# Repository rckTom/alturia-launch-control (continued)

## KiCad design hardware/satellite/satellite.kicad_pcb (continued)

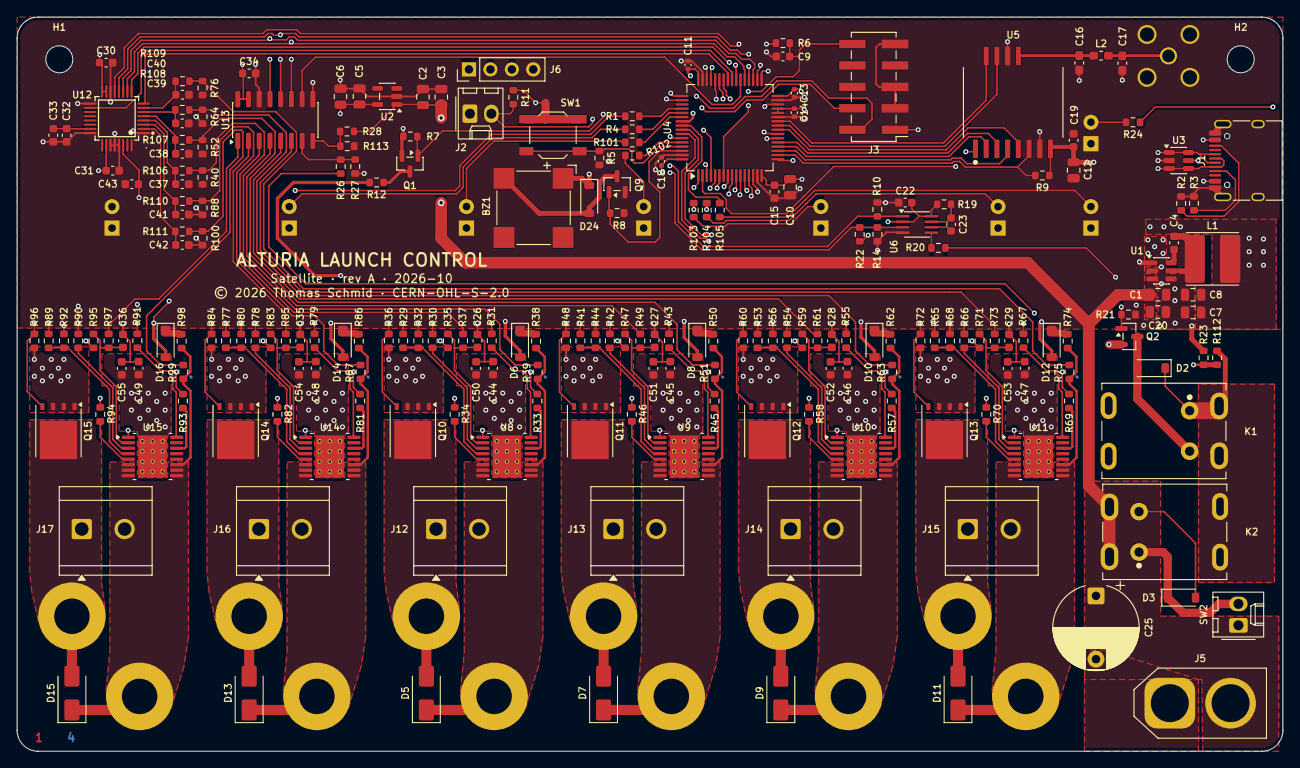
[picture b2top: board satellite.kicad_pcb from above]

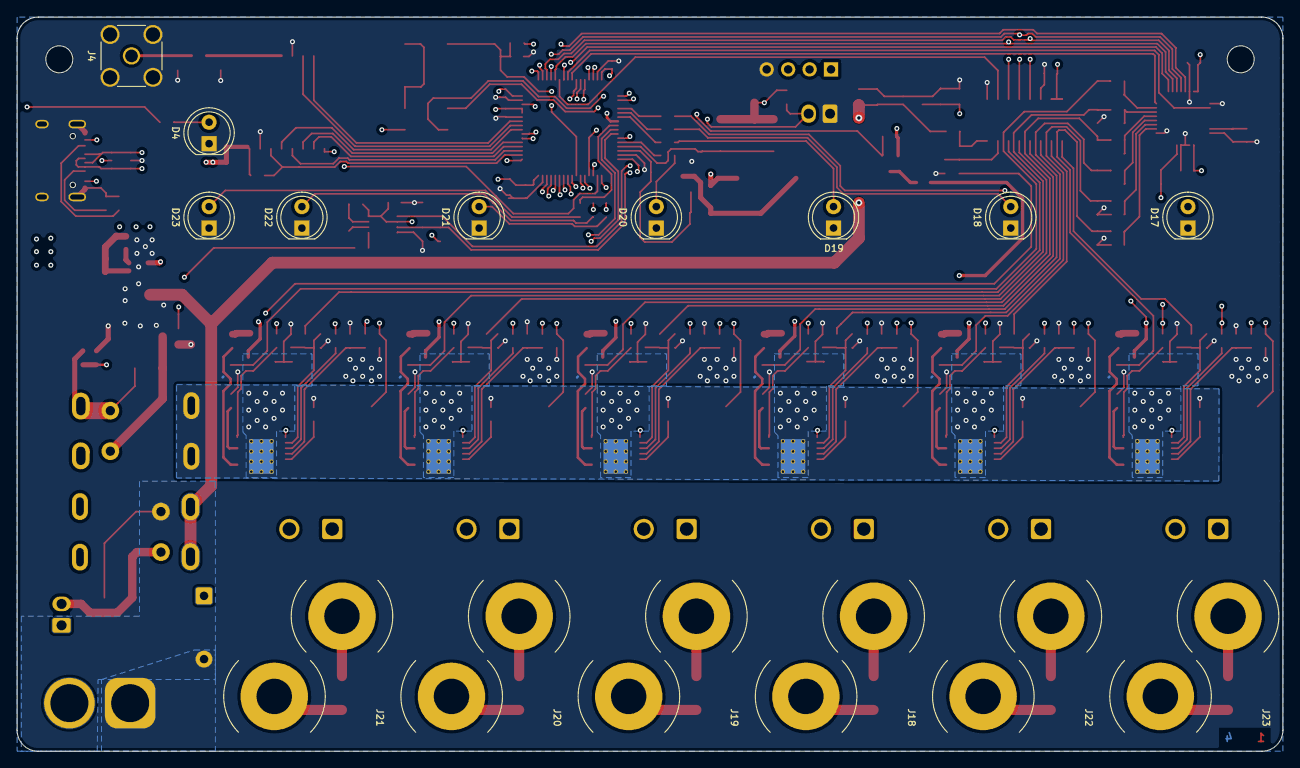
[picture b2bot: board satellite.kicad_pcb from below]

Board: 4 copper layers, 150.0 x 87.0 mm, 233 parts (15 on the bottom side), 156 nets.

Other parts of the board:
C12: 10u; C_0805_2012Metric
C19, C43, C44, C45, C46, C47, C48, C49, C50, C51, C52, C53, C54, C55: 100n; C_0603_1608Metric
R11: 10k 1%; R_0603_1608Metric

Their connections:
+3V3: C12.1, C19.1, R11.1; also elsewhere on the board
CONT_TEST_REQ: R11.2; also elsewhere on the board
GND: C12.2, C19.2, C43.2, C44.1, C45.1, C46.1, C47.1, C48.1, C49.1, C50.1, C51.1, C52.1, C53.1, C54.1, C55.1; also elsewhere on the board
V_PYRO_ARMED: C44.2, C45.2, C46.2, C47.2, C48.2, C49.2, C50.2, C51.2, C52.2, C53.2, C54.2, C55.2; also elsewhere on the board
V_TEST: C43.1; also elsewhere on the board

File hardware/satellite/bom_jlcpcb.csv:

"Comment","Designator","Footprint","LCSC Part #"
"Buzzer","BZ1","MagneticBuzzer_CUI_CMT-8504-100-SMT","C94599"
"10u","C1,C2,C5,C12,C20","C_0805_2012Metric","C440198"
"1u","C3","C_0805_2012Metric","C28323"
"100n","C4,C9,C19,C22,C26,C27,C28,C29,C30,C33,C35,C36,C37,C38,C39,C40,C41,C42,C43,C44,C45,C46,C47,C48,C49,C50,C51,C52,C53,C54,C55","C_0603_1608Metric","C14663"
"2.2u","C6","C_0805_2012Metric","C19110"
"22u","C7,C8","C_0805_2012Metric","C45783"
"4.7uF","C10","C_0805_2012Metric","C98195"
"100nF","C11,C13,C14,C18","C_0402_1005Metric","C307331"
"1u","C15,C23,C32,C34","C_0603_1608Metric","C5199872"
"330n","C31","C_0603_1608Metric","C107070"
"1N4148W","D2,D3,D6,D8,D10,D12,D14,D16,D24","D_SOD-123","C81598"
"SS34","D5,D7,D9,D11,D13,D15","D_SMA","C8678"
"TYPE-C 16P","J1","USB_C_Receptacle_HRO_TYPE-C-31-M-12","C2765186"
"ACTL3CR3V","K1,K2","RELAY-TH_ACTL3CR3","C6118826"
"10uH","L1","L_Cenker_CKCS6045","C168076"
"AO3401A","Q1","SOT-23","C15127"
"AO3400A","Q2,Q9","SOT-23","C20917"
"CSD17307Q5A","Q10,Q11,Q12,Q13,Q14,Q15","TDSON-8-1","C139362"
"560 1%","R1,R4,R35,R47,R59,R71,R83,R95,R101,R102,R103,R104,R105","R_0603_1608Metric","C23204"
"5.1k 1%","R2,R3","R_0603_1608Metric","C23186"
"10k 1%","R5,R6,R7,R8,R9,R10,R11,R14,R21,R32,R33,R36,R44,R45,R48,R56,R57,R60,R68,R69,R72,R80,R81,R84,R92,R93,R96,R106,R107,R108,R109,R110,R111","R_0603_1608Metric","C25804"
"270","R12","R_0603_1608Metric","C22966"
"150k 1%","R19","R_0603_1608Metric","C22807"
"1k 1%","R20,R23,R27,R38,R40,R50,R52,R62,R64,R74,R76,R86,R88,R98,R100,R113","R_0603_1608Metric","C21190"
"3k3 1%","R24,R26,R28,R39,R51,R63,R75,R87,R99,R112","R_0603_1608Metric","C22978"
"100 1%","R29,R30,R31,R37,R41,R42,R43,R49,R53,R54,R55,R61,R65,R66,R67,R73,R77,R78,R79,R85,R89,R90,R91,R97","R_0603_1608Metric","C22775"
"6k8 1%","R34,R46,R58,R70,R82,R94","R_0603_1608Metric","C23212"
"BOOT0","SW1","SW_SPST_TL3342","C318884"
"AP63203WU","U1","TSOT-23-6","C780769"
"TPS70933DBVR","U2","SOT-23-5","C89347"
"USBLC6-2SC6","U3","SOT-23-6","C2687116"
"STM32G474RET6","U4","LQFP-64_10x10mm_P0.5mm","C521608"
"SN74LVC1G123","U6","SSOP-8_2.95x2.8mm_P0.65mm","C123302"
"TPS1HB08AQPWPRQ1","U8,U9,U10,U11,U14,U15","HTSSOP-16-1EP_4.4x5mm_P0.65mm_EP3.4x5mm_Mask2.78x3.37mm_ThermalVias03","C3019223"
"ADS124S08IPBSR","U12","TQFP-32_L5.0-W5.0-P0.50-LS7.0-TL","C2870171"
"MCP3208","U13","SOIC-16_3.9x9.9mm_P1.27mm","C626764"

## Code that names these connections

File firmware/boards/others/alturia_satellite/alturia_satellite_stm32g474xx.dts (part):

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 * schematic (CH(6 - n) is channel n).
 *
 * There is no HSE crystal: the core runs from HSI16 through the PLL, USB
 * from HSI48 trimmed by CRS (board.c). PF0/PF1 are channel 6's enables and
 * PC14 is ARM_ENABLE, so neither clk_hse nor clk_lse may be enabled.
 */

/dts-v1/;
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		compatible = "gpio-leds";

		status_led: status_led {
			gpios = <&gpiob 3 GPIO_ACTIVE_HIGH>;	/* LED_STATUS, D23 */
		};
	};

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	chan_leds {
		compatible = "gpio-leds";

		chan_led1: chan_led1 { gpios = <&gpioa 8 GPIO_ACTIVE_HIGH>; };	/* LED_CHN_6 */
		chan_led2: chan_led2 { gpios = <&gpioa 9 GPIO_ACTIVE_HIGH>; };	/* LED_CHN_5 */
		chan_led3: chan_led3 { gpios = <&gpiob 7 GPIO_ACTIVE_HIGH>; };	/* LED_CHN_4 */
		chan_led4: chan_led4 { gpios = <&gpioc 12 GPIO_ACTIVE_HIGH>; };	/* LED_CHN_3 */
		chan_led5: chan_led5 { gpios = <&gpioc 11 GPIO_ACTIVE_HIGH>; };	/* LED_CHN_2 */
		chan_led6: chan_led6 { gpios = <&gpioc 10 GPIO_ACTIVE_HIGH>; };	/* LED_CHN_1 */
	};

	/* Pyro channel control lines: TPS1HB08 enables (through 100 R) and the
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	pyro_enables {
		compatible = "gpio-leds";

		en_h1: en_h1 { gpios = <&gpioa 3 GPIO_ACTIVE_HIGH>; };	/* ENABLE_P6_HIGH */
		en_h2: en_h2 { gpios = <&gpioc 5 GPIO_ACTIVE_HIGH>; };	/* ENABLE_P5_HIGH */
		en_h3: en_h3 { gpios = <&gpioa 1 GPIO_ACTIVE_HIGH>; };	/* ENABLE_P4_HIGH */
		en_h4: en_h4 { gpios = <&gpioc 3 GPIO_ACTIVE_HIGH>; };	/* ENABLE_P3_HIGH */
		en_h5: en_h5 { gpios = <&gpioc 1 GPIO_ACTIVE_HIGH>; };	/* ENABLE_P2_HIGH */
		en_h6: en_h6 { gpios = <&gpiof 1 GPIO_ACTIVE_HIGH>; };	/* ENABLE_P1_HIGH */
		en_l1: en_l1 { gpios = <&gpioc 4 GPIO_ACTIVE_HIGH>; };	/* ENABLE_P6_LOW */
		en_l2: en_l2 { gpios = <&gpioa 2 GPIO_ACTIVE_HIGH>; };	/* ENABLE_P5_LOW */
		en_l3: en_l3 { gpios = <&gpioa 0 GPIO_ACTIVE_HIGH>; };	/* ENABLE_P4_LOW */
		en_l4: en_l4 { gpios = <&gpioc 2 GPIO_ACTIVE_HIGH>; };	/* ENABLE_P3_LOW */
		en_l5: en_l5 { gpios = <&gpioc 0 GPIO_ACTIVE_HIGH>; };	/* ENABLE_P2_LOW */
		en_l6: en_l6 { gpios = <&gpiof 0 GPIO_ACTIVE_HIGH>; };	/* ENABLE_P1_LOW */
		hs_latch: hs_latch {
			gpios = <&gpiob 4 GPIO_ACTIVE_HIGH>;	/* COMMON_HIGH_SIDE_LATCH */
		};
		hs_dia_en: hs_dia_en {
			gpios = <&gpiob 5 GPIO_ACTIVE_HIGH>;	/* COMMON_HIGH_SIDE_DIA_EN */
		};
	};

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		compatible = "gpio-leds";

		arm_pump: arm_pump {
			gpios = <&gpiob 6 GPIO_ACTIVE_HIGH>;	/* ARM_PUMP -> U6 A */
		};
		arm_enable: arm_enable {
			gpios = <&gpioc 14 GPIO_ACTIVE_HIGH>;	/* ARM_ENABLE -> U6 CLR */
		};
		cont_en: cont_en {
			gpios = <&gpioa 10 GPIO_ACTIVE_LOW>;	/* CONT_EN, Q1 gate */
		};
	};

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		compatible = "gpio-keys";

		pair_button: pair_button {
			gpios = <&gpioc 15 GPIO_ACTIVE_LOW>;	/* CONT_TEST_REQ */
			zephyr,code = <INPUT_KEY_0>;
		};
	};

	/* VKEY through the 3k3/1k divider: the key relay K2 has closed. PD2
	 * shares EXTI line 2 with LORA_DIO1 on PB2, so it is polled.
	 */
	key_switch {
		compatible = "gpio-keys";
		polling-mode;

		key_enabled: key_enabled {
			gpios = <&gpiod 2 GPIO_ACTIVE_HIGH>;	/* KEY_ENABLED */
			zephyr,code = <INPUT_KEY_1>;
		};
	};
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
/* Schematic net names, so the GPIO shell can address pins by them. */
&gpioa {
	gpio-line-names = "ENABLE_P4_LOW", "ENABLE_P4_HIGH", "ENABLE_P5_LOW", "ENABLE_P6_HIGH",
			  "LORA_NSS", "LORA_SCK", "LORA_MISO", "LORA_MOSI",
			  "LED_CHN_6", "LED_CHN_5", "CONT_EN", "USB_DN",
			  "USB_DP", "SWDIO", "SWCLK", "";
};

&gpiob {
	gpio-line-names = "LORA_RST", "LORA_BUSY", "LORA_DIO1", "LED_STATUS",
			  "COMMON_HIGH_SIDE_LATCH", "COMMON_HIGH_SIDE_DIA_EN", "ARM_PUMP", "LED_CHN_4",
			  "BOOT0", "BUZZER", "U0RXD", "U0TXD",
			  "SPI_ADC_24BIT_CS", "SPI_ADC_CLK", "SPI_ADC_MISO", "SPI_ADC_MOSI";
};

&gpioc {
	gpio-line-names = "ENABLE_P2_LOW", "ENABLE_P2_HIGH", "ENABLE_P3_LOW", "ENABLE_P3_HIGH",
			  "ENABLE_P6_LOW", "ENABLE_P5_HIGH", "SPI_ADC_12BIT_CS", "24BIT_ADC_DRDY",
			  "24BIT_ADC_RESET", "24BIT_ADC_START", "LED_CHN_1", "LED_CHN_2",
			  "LED_CHN_3", "LORA_RF_SW", "ARM_ENABLE", "CONT_TEST_REQ";
};

&gpiod {
	gpio-line-names = "", "", "KEY_ENABLED";
};

&gpiof {
	gpio-line-names = "ENABLE_P1_LOW", "ENABLE_P1_HIGH";
};

&clk_lsi {
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&spi1 {
	pinctrl-0 = <&spi1_sck_pa5 &spi1_miso_pa6 &spi1_mosi_pa7>;
	pinctrl-names = "default";
	cs-gpios = <&gpioa 4 GPIO_ACTIVE_LOW>;	/* LORA_NSS, 10k pull-up */
	status = "okay";

	lora: sx1262@0 {
		compatible = "semtech,sx1262";
		reg = <0>;
		spi-max-frequency = <DT_FREQ_M(8)>;
		reset-gpios = <&gpiob 0 GPIO_ACTIVE_LOW>;	/* LORA_RST */
		busy-gpios = <&gpiob 1 GPIO_ACTIVE_HIGH>;	/* LORA_BUSY */
		dio1-gpios = <&gpiob 2 GPIO_ACTIVE_HIGH>;	/* LORA_DIO1 */
		antenna-enable-gpios = <&gpioc 13 GPIO_ACTIVE_HIGH>;	/* LORA_RF_SW */
		dio2-tx-enable;
		dio3-tcxo-voltage = <SX126X_DIO3_TCXO_1V8>;
		tcxo-power-startup-delay-ms = <5>;
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&spi2 {
	pinctrl-0 = <&spi2_sck_pb13 &spi2_miso_pb14 &spi2_mosi_pb15>;
	pinctrl-names = "default";
	cs-gpios = <&gpiob 12 GPIO_ACTIVE_LOW>,	/* SPI_ADC_24BIT_CS */
		   <&gpioc 6 GPIO_ACTIVE_LOW>;	/* SPI_ADC_12BIT_CS */
	status = "okay";

	adc_continuity: ads124s08@0 {
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
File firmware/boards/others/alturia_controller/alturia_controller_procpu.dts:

/*
 * Alturia Launch Control controller, rev A
 * (hardware/controller/pcb, ESP32-S3-WROOM-1-N16R2).
 *
 * Console and shell are on USB-C, which goes straight to the ESP32-S3's
 * USB Serial/JTAG. UART0's pins drive the LCD, so there is no UART.
 *
 * The controls are pushbuttons to GND with no external pull-ups. The front
 * panel has no arm key switch.
 */
/dts-v1/;

#include <espressif/esp32s3/esp32s3.dtsi>
#include <zephyr/dt-bindings/input/input-event-codes.h>
#include <zephyr/dt-bindings/lora/sx126x.h>
#include <zephyr/dt-bindings/pwm/pwm.h>
#include <espressif/partitions_0x0_amp_16M.dtsi>
#include "alturia_controller-pinctrl.dtsi"

/ {
	model = "Alturia Launch Control controller";
	compatible = "alturia,controller";

	aliases {
		led0 = &status_led;
		lora0 = &lora;
		buzzer = &buzzer;
		watchdog0 = &wdt0;
		fuel-gauge0 = &fuel_gauge;
		charger0 = &charger;
	};

	chosen {
		zephyr,sram = &sram1;
		zephyr,console = &usb_serial;
		zephyr,shell-uart = &usb_serial;
		zephyr,flash = &flash0;
		zephyr,code-partition = &slot0_partition;
		zephyr,display = &sharp_lcd;
	};

	leds {
		compatible = "gpio-leds";

		status_led: status_led {
			gpios = <&gpio1 10 GPIO_ACTIVE_HIGH>;	/* IO42, STATUS_LED */
		};
	};

	/* Passive magnetic buzzer QMB-09B-03; it needs a tone, not a level. */
	buzzer: buzzer {
		compatible = "pwm-buzzer";
		pwms = <&ledc0 0 PWM_HZ(4000) PWM_POLARITY_NORMAL>;	/* IO46 */
	};

	/* Key codes are the ones the controller app listens for. */
	ctrl_keys: ctrl_keys {
		compatible = "gpio-keys";
		debounce-interval-ms = <20>;

		/* Delock 22032 pushbuttons on J3 / J2 */
		arm_button {
			gpios = <&gpio0 8 (GPIO_PULL_UP | GPIO_ACTIVE_LOW)>;	/* KEY_ARM */
			zephyr,code = <INPUT_KEY_A>;
		};

		fire_button {
			gpios = <&gpio0 5 (GPIO_PULL_UP | GPIO_ACTIVE_LOW)>;	/* KEY_FIRE */
			zephyr,code = <INPUT_KEY_SPACE>;
		};

		fill_button {
			gpios = <&gpio0 3 (GPIO_PULL_UP | GPIO_ACTIVE_LOW)>;	/* KEY_FILL */
			zephyr,code = <INPUT_KEY_F>;
		};

		vent_button {
			gpios = <&gpio0 6 (GPIO_PULL_UP | GPIO_ACTIVE_LOW)>;	/* KEY_VENT */
			zephyr,code = <INPUT_KEY_V>;
		};

		/* D-pad SW1..SW6 */
		key_up {
			gpios = <&gpio0 1 (GPIO_PULL_UP | GPIO_ACTIVE_LOW)>;	/* KEY_UP */
			zephyr,code = <INPUT_KEY_UP>;
		};

		key_down {
			gpios = <&gpio0 4 (GPIO_PULL_UP | GPIO_ACTIVE_LOW)>;	/* KEY_DOWN */
			zephyr,code = <INPUT_KEY_DOWN>;
		};

		key_left {
			gpios = <&gpio0 2 (GPIO_PULL_UP | GPIO_ACTIVE_LOW)>;	/* KEY_LEFT */
			zephyr,code = <INPUT_KEY_LEFT>;
		};

		key_right {
			gpios = <&gpio0 7 (GPIO_PULL_UP | GPIO_ACTIVE_LOW)>;	/* KEY_RIGHT */
			zephyr,code = <INPUT_KEY_RIGHT>;
		};

		key_enter {
			gpios = <&gpio0 0 (GPIO_PULL_UP | GPIO_ACTIVE_LOW)>;	/* KEY_ENTER, BOOT strap */
			zephyr,code = <INPUT_KEY_ENTER>;
		};

		key_back {
			gpios = <&gpio0 9 (GPIO_PULL_UP | GPIO_ACTIVE_LOW)>;	/* KEY_BACK */
			zephyr,code = <INPUT_KEY_BACK>;
		};

		/* SW101 through Q105, 100k pull-up on board. Held for 6-9 s, the
		 * latch switches off by itself. A press held since power-on is
		 * not reported: gpio-keys only reports changes.
		 */
		power_button {
			gpios = <&gpio0 18 GPIO_ACTIVE_LOW>;	/* PWR_BTN */
			zephyr,code = <INPUT_KEY_POWER>;
		};
	};

	zephyr,user {
		/* Soft power latch (power_latch sheet): PWR_OFF high drops the
		 * 3V3_EN latch, unless the power button holds it.
		 */
		pwr-off-gpios = <&gpio0 21 GPIO_ACTIVE_HIGH>;
		/* BQ24296M PG: low while USB power is good */
		usb-pgood-gpios = <&gpio1 9 GPIO_ACTIVE_LOW>;	/* IO41 */
	};
};

/* 160 MHz instead of 240: the UI and the link need far less, and the CPU
 * mostly sleeps, so it is the awake current that counts.
 */
&cpu0 {
	clock-frequency = <ESP32_CLK_CPU_PLL_160M>;
};

/* Wakes light sleep (CONFIG_PM) for the kernel's next timeout */
&rtc_timer {
	status = "okay";
	wakeup-source;
};

&flash0 {
	reg = <0x0 DT_SIZE_M(16)>;
	ranges = <0x0 0x0 DT_SIZE_M(16)>;
};

&usb_serial {
	status = "okay";
};

&gpio0 {
	status = "okay";
	gpio-line-names = "KEY_ENTER", "KEY_UP", "KEY_LEFT", "KEY_FILL",
			  "KEY_DOWN", "KEY_FIRE", "KEY_ARM", "KEY_RIGHT",
			  "KEY_VENT", "KEY_BACK", "LORA_NSS", "SPI_MOSI",
			  "SPI_SCK", "SPI_MISO", "LORA_BUSY", "LORA_DIO1",
			  "LORA_RST", "LORA_RF_SW", "PWR_BTN", "USB_DN",
			  "USB_DP", "PWR_OFF";
};

&gpio1 {
	status = "okay";
	gpio-line-names = "", "", "", "", "", "",
			  "I2C_SDA", "I2C_SCL", "GAUGE_ALRT", "USB_PGOOD",
			  "STATUS_LED", "LCD_SCK", "LCD_MOSI", "LCD_CS",
			  "BUZZER", "", "LCD_DISP";
};

&i2c0 {
	status = "okay";
	clock-frequency = <I2C_BITRATE_STANDARD>;
	pinctrl-0 = <&i2c0_default>;
	pinctrl-names = "default";

	fuel_gauge: max17048@36 {
		compatible = "maxim,max17048";
		reg = <0x36>;
	};

	/* Programmed by the driver at boot (CONFIG_CHARGER): 0.25 C for the
	 * 4 Ah 606090 cell, and no I2C watchdog, so the charger stays in host
	 * mode and keeps its input limit.
	 */
	charger: bq24296m@6b {
		compatible = "ti,bq24296m";
		reg = <0x6b>;
		constant-charge-current-max-microamp = <1024000>;
		constant-charge-voltage-max-microvolt = <4208000>;
		watchdog-timeout-ms = <0>;
	};
};

/* Wio-SX1262. DIO2 selects TX inside the module, RF_SW powers the switch,
 * which the native driver drives as antenna-enable.
 */
&spi2 {
	#address-cells = <1>;
	#size-cells = <0>;
	status = "okay";
	pinctrl-0 = <&spim2_default>;
	pinctrl-names = "default";
	cs-gpios = <&gpio0 10 GPIO_ACTIVE_LOW>;	/* LORA_NSS, 10k pull-up */

	lora: sx1262@0 {
		compatible = "semtech,sx1262";
		reg = <0>;
		spi-max-frequency = <DT_FREQ_M(8)>;
		reset-gpios = <&gpio0 16 GPIO_ACTIVE_LOW>;	/* LORA_RST */
		busy-gpios = <&gpio0 14 GPIO_ACTIVE_HIGH>;	/* LORA_BUSY */
		dio1-gpios = <&gpio0 15 GPIO_ACTIVE_HIGH>;	/* LORA_DIO1 */
		antenna-enable-gpios = <&gpio0 17 GPIO_ACTIVE_HIGH>;	/* LORA_RF_SW */
		dio2-tx-enable;
		dio3-tcxo-voltage = <SX126X_DIO3_TCXO_1V8>;
		tcxo-power-startup-delay-ms = <5>;
	};
};

/* Adafruit 4694 (LS027B7DH01, 400x240). EXTCOMIN and EXTMODE are open, so
 * VCOM is inverted over SPI. CS has a 10k pull-down.
 */
&spi3 {
	#address-cells = <1>;
	#size-cells = <0>;
	status = "okay";
	pinctrl-0 = <&spim3_default>;
	pinctrl-names = "default";
	cs-gpios = <&gpio1 13 GPIO_ACTIVE_HIGH>;	/* IO45, LCD_CS */

	sharp_lcd: ls0xx@0 {
		compatible = "sharp,ls0xx";
		reg = <0>;
		spi-max-frequency = <DT_FREQ_M(2)>;
		width = <400>;
		height = <240>;
		disp-en-gpios = <&gpio1 16 GPIO_ACTIVE_HIGH>;	/* IO48, LCD_DISP */
		serial-vcom-inversion;
	};
};

&ledc0 {
	status = "okay";
	pinctrl-0 = <&ledc0_default>;
	pinctrl-names = "default";
	#address-cells = <1>;
	#size-cells = <0>;

	channel0@0 {
		reg = <0x0>;
		timer = <0>;
	};
};

&wdt0 {
	status = "okay";
};

&trng0 {
	status = "okay";
};

&timer0 {
	status = "disabled";
};

&timer1 {
	status = "disabled";
};

&timer2 {
	status = "disabled";
};

&timer3 {
	status = "disabled";
};
